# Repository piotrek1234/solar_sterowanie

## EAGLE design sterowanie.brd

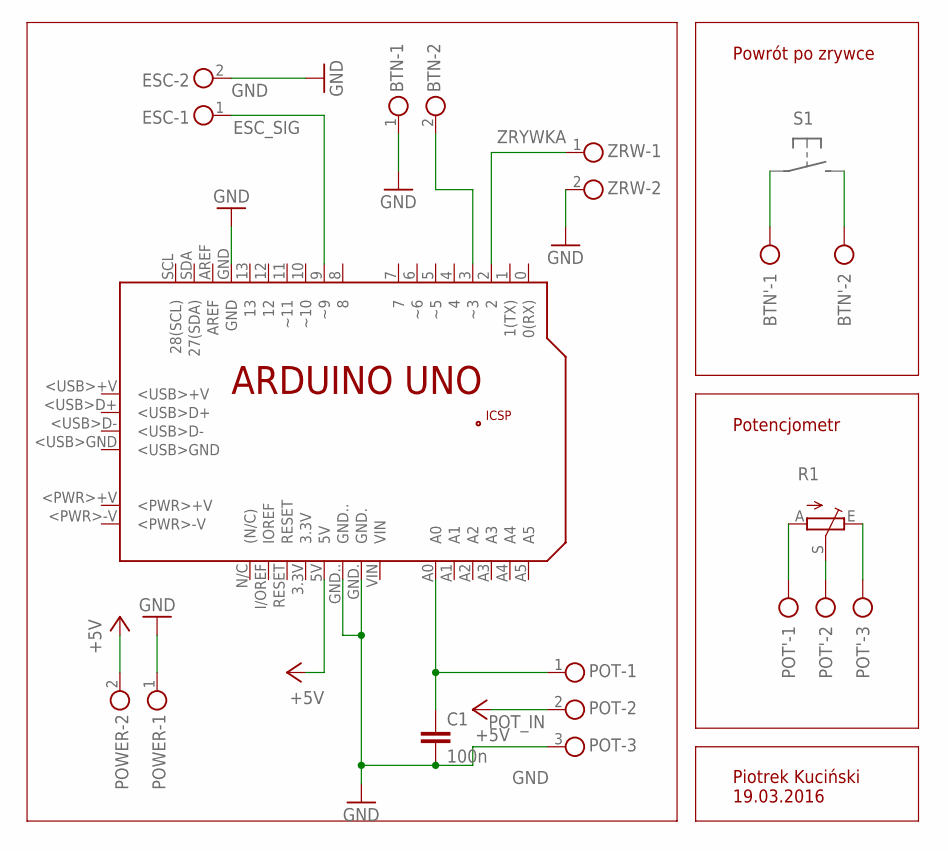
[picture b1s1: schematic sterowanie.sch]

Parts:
BTN: AKL59-02; 2POL35
BTN': AK300/2
C1: 100n; C1206
ESC: AKL59-02; 2POL35
PCB1: ARDUINO_UNO
POT: AKL59-03; 3POL35
POT': AK300/3
POWER: AKL59-02; 2POL35
R1: TRIM_EU-B90P; SP19L
ZRW: AKL59-02; 2POL35

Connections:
+5V: PCB1.5V, POT.2, POWER.2
ESC_SIG: ESC.1, PCB1.9 (~9)
GND: BTN.1, C1.2, ESC.2, PCB1.GND, PCB1.GND., PCB1.GND.., POT.3, POWER.1, ZRW.2
unnamed: BTN.2, PCB1.3 (~3)
unnamed: POT'.3, R1.E
unnamed: POT'.1, R1.A
unnamed: POT'.2, R1.S
POT_IN: C1.1, PCB1.A0, POT.1
ZRYWKA: PCB1.2, ZRW.1

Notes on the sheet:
Powrót po zrywce
Potencjometr
Piotrek Kuciński 19.03.2016

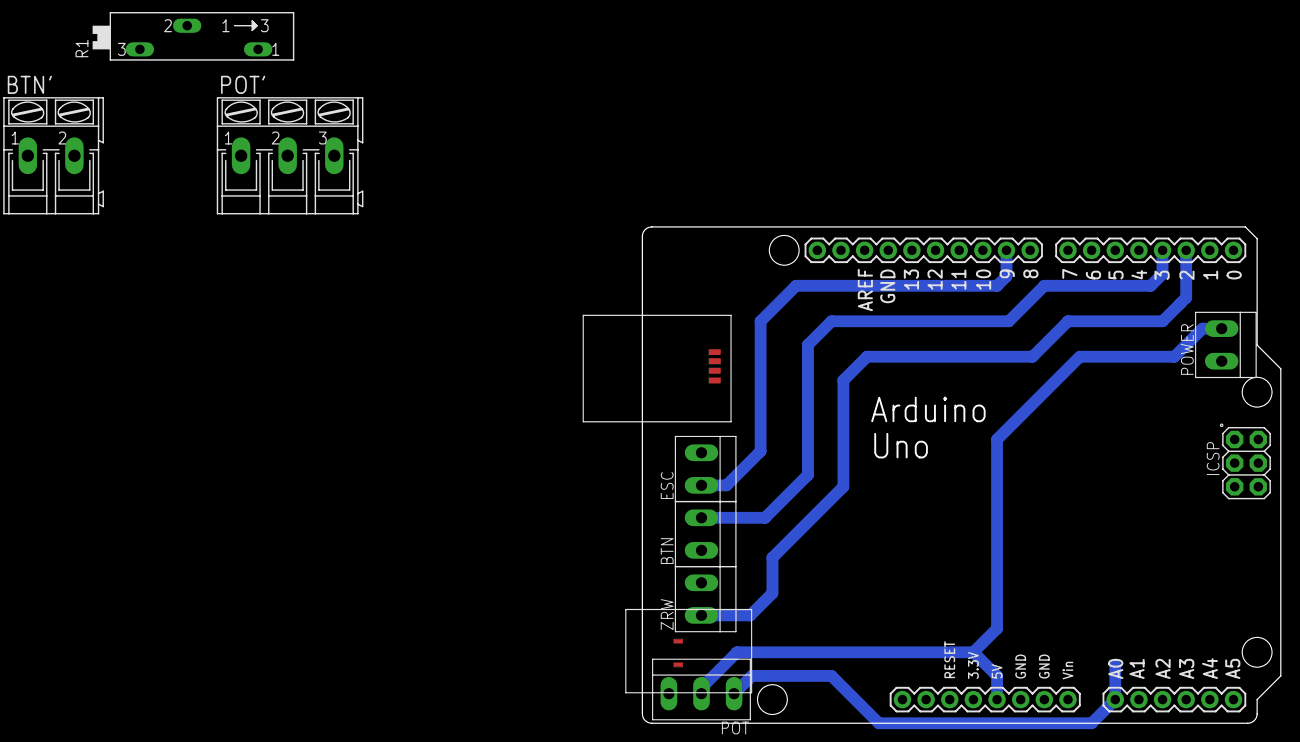
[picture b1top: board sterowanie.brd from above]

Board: 2 copper layers, 68.6 x 53.3 mm, 10 parts (1 on the bottom side), 9 nets.

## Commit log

2016-03-19 Added files via upload
2016-04-06 poprawiony schemat, dodane PCB jako shield do Arduino
2016-05-08 program przepisany do C (na Atmel Studio)
